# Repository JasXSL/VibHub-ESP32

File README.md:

# VibHub-ESP32
Beefing up the HW of VibHub

This is the firmware for the ESP32 version.
If you're looking for the API documentation, you can find that on the original VibHub client git: 
https://github.com/JasXSL/VibHub-Client/wiki

Official website: https://vibhub.io

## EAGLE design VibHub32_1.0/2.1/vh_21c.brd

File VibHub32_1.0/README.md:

# VibHub ESP32 Board 2.x

## 2.0a (Shipped 2019)

ESP32 based dev boards shipped in 2019
Replaced by 2.1

## 2.1 rev.A (Unreleased)

Complete board redesign

Add: Lower BOM cost
Changed: Smaller board size
Changed: Moved all buttons to top side of board
Changed: Removed duplicate vibe ports, replaced with combined footprint, can have 4 ports of any combination of 2.5mm and USB
Removed: Extra debug headers and LEDs

Bug: Missing trace that prevents USB-UART chip from powering

## 2.1 rev.B (Unreleased)

Unreleased
50% board redesign due to new battery holder to replace previous that became unavailable

Add: Second RGB LED
Add: More mounting holes
Add: True auto power off while on battery
Add: Side firing LEDs on driver outputs (Only works if drivers are in "forward")
Changed: Replaced electrolytic cap with tantalum to reduce component side height clearance

Bug: High leakage current through TX line while running on battery

## 2.1 rev.C (In Production)

First batch of 30 dev boards currently in production as of 2020-03-04, should be shipping by mid March

Bug: Designator and pin 1 marking missing on D1

## 2.1 rev.C2 (Design In Progress)

Tentative revision for next batch
Identical to rev.C with only silkscreen modifications

## 2.1 rev.D (Planning)

Future TODO stuff

TODO: Replace DRV8833 footprint with QFN16 after supply of HTSSOP16 parts has been used. The HTSSOP16/QFN16 combo footprint works but is more difficult to reflow than needed.

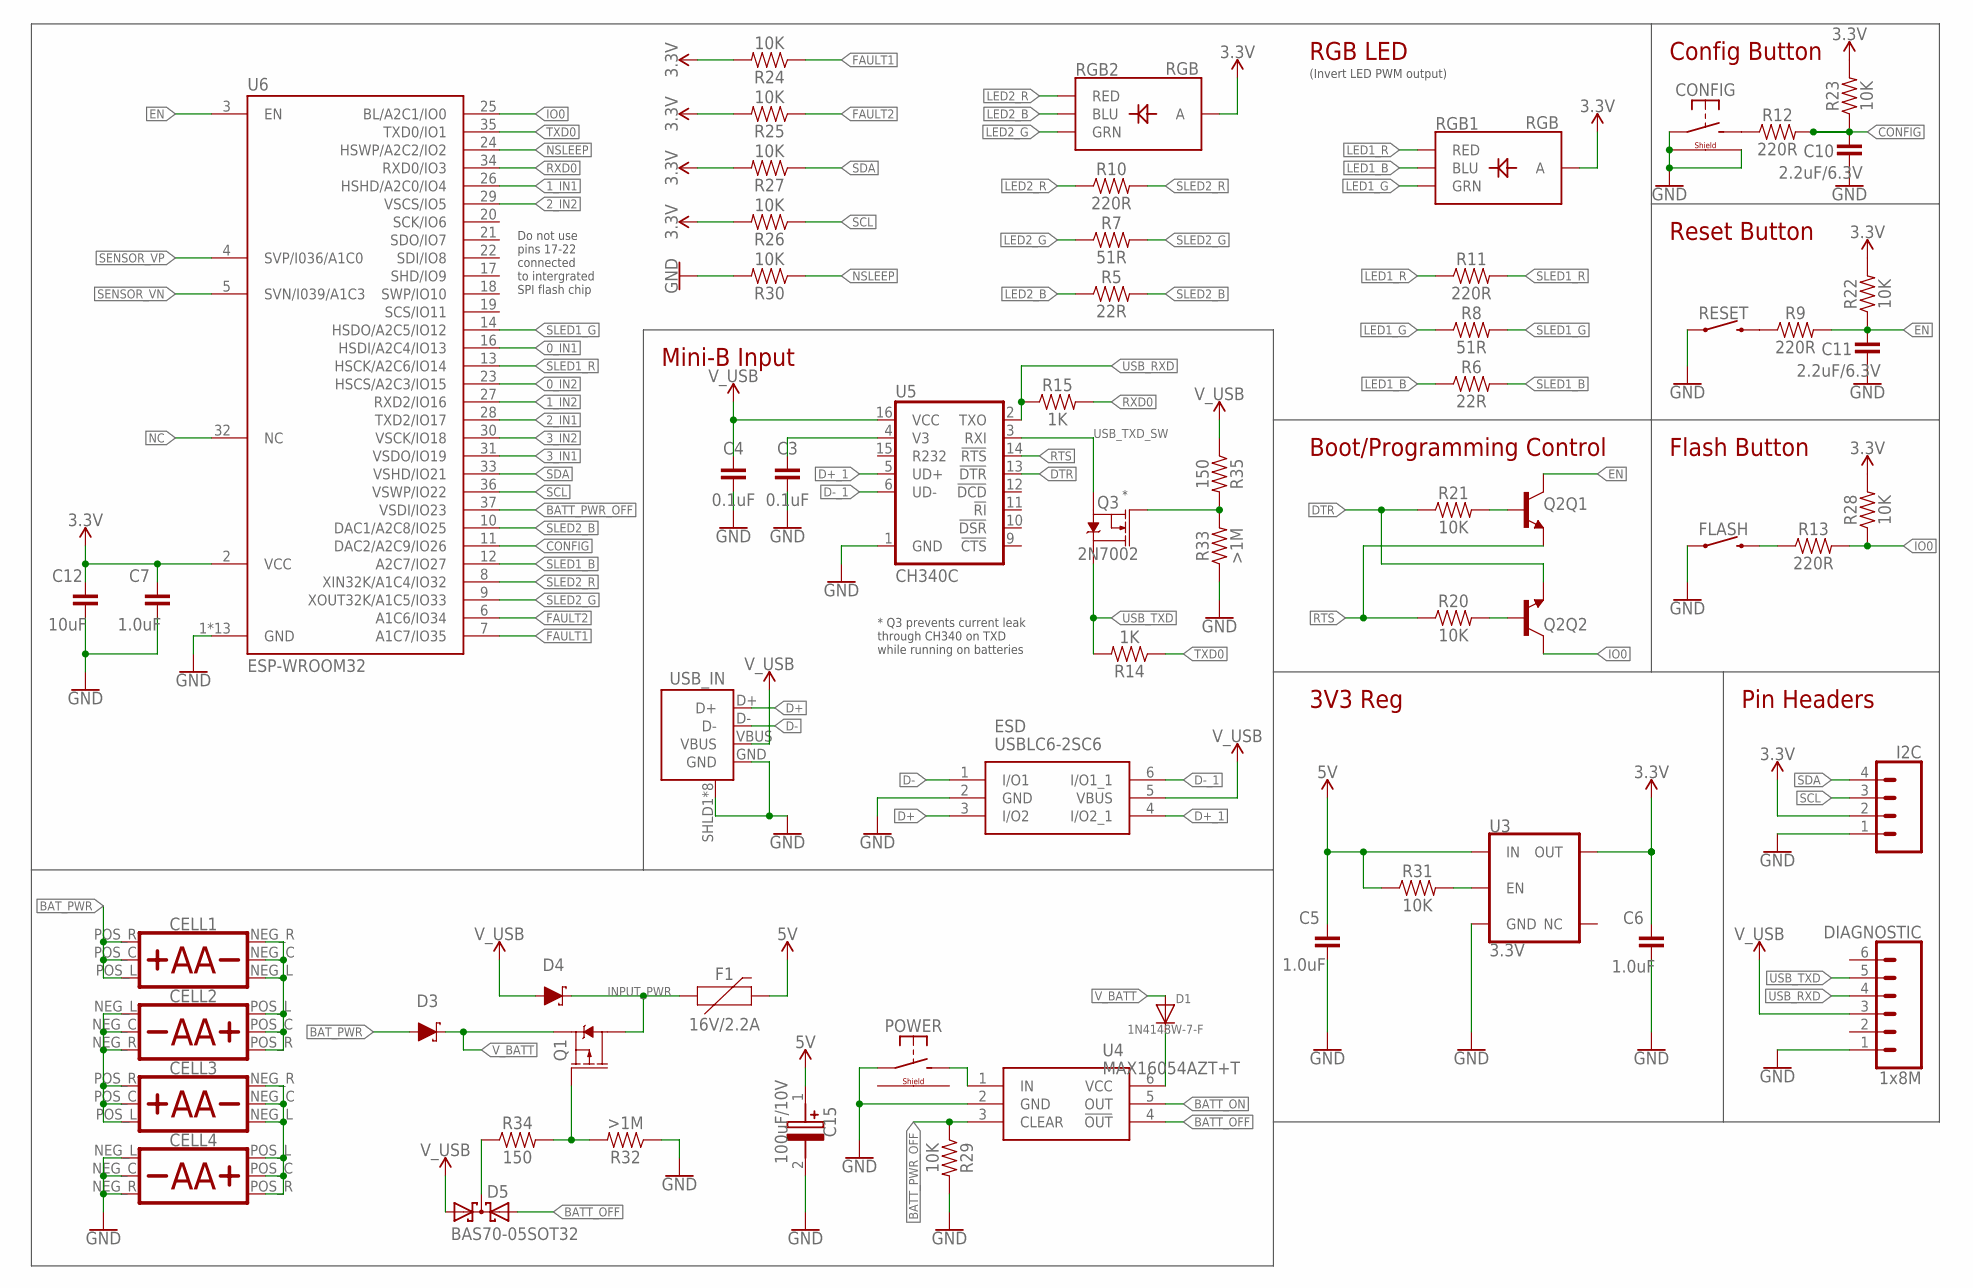
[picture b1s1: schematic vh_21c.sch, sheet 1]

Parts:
C3, C4: 0.1uF; C0805
C5, C6, C7: 1.0uF; C0805
C10, C11: 2.2uF/6.3V; C0805
C12: 10uF; C0805
C15: 100uF/10V; CAPPM6032X270N
CELL1, CELL2, CELL3, CELL4: AA_590_596
CONFIG: MOMENTARY-SWITCH-SPST-RIGHTSQ75; SW6X6_RIGHT_SQ73
D1: 1N4148W-7-F; SOD-123
D3, D4: 3A/40V/500mV; SMA-DIODE
D5: BAS70-05SOT32; SOT91P240X110-3
DIAGNOSTIC: 1x8M; 1X06_LOCK
ESD: USBLC6-2SC6; SOT95P280X145-6N
F1: 16V/2.2A; FUSC7035X90
FLASH: MOMENTARY-SWITCH-SPST-SMD-6.0X3.5MM; TACTILE_SWITCH_SMD_6.0X3.5MM
I2C: CONN_04; 1X04
POWER: MOMENTARY-SWITCH-SPST-RIGHTSQ75; SW6X6_RIGHT_SQ73
Q1: MOSFET_PCH-DMG2305UX-13; SOT91P240X110-3
Q2: TRANS_NPN_DUAL-MBT3904DW1T1; SC70-6
Q3: 2N7002; SOT23-3
R5, R6: 22R; 0805
R7, R8: 51R; 0805
R9, R10, R11, R12, R13: 220R; 0805
R14, R15: 1K; 0805
R20, R21, R22, R23, R24, R25, R26, R27, R28, R29, R30, R31: 10K; 0805
R32, R33: >1M; 0805
R34, R35: 150; 0805
RESET: MOMENTARY-SWITCH-SPST-SMD-6.0X3.5MM; TACTILE_SWITCH_SMD_6.0X3.5MM
RGB1, RGB2: RGB; P-LCC-4-3
U3: 3.3V; SOT23-5
U4: MAX16054AZT+T; SOT95P275X110-6N
U5: CH340C; SO016
U6: ESP-WROOM32
USB_IN: USB-MICROB-2; USB-MICROB-10118194

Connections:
0_IN1: U6.16 (HSDI/A2C4/IO13); also elsewhere on the board
0_IN2: U6.23 (HSCS/A2C3/IO15); also elsewhere on the board
1_IN1: U6.26 (HSHD/A2C0/IO4); also elsewhere on the board
1_IN2: U6.27 (RXD2/IO16); also elsewhere on the board
2_IN1: U6.28 (TXD2/IO17); also elsewhere on the board
2_IN2: U6.29 (VSCS/IO5); also elsewhere on the board
3.3V: C6.1, C7.1, C12.1, I2C.2, R22.2, R23.2, R24.2, R25.2, R26.2, R27.2, R28.2, RGB1.4 (A), RGB2.4 (A), U3.5 (OUT), U6.2 (VCC)
3_IN1: U6.31 (VSDO/IO19); also elsewhere on the board
3_IN2: U6.30 (VSCK/IO18); also elsewhere on the board
5V: C5.1, C15.1 (+), F1.2, R31.1, U3.1 (IN); also elsewhere on the board
BATT_OFF: D5.2 (A2), U4.4 (!OUT)
BATT_ON: U4.5 (OUT)
BATT_PWR_OFF: R29.1, U4.3 (CLEAR), U6.37 (VSDI/IO23)
BAT_PWR: CELL1.POS_C, CELL1.POS_L, CELL1.POS_R, D3.A
CONFIG: C10.1, R12.2, R23.1, U6.11 (DAC2/A2C9/IO26)
D+: ESD.3 (I/O2), USB_IN.D+
D+_1: ESD.4 (I/O2_1), U5.5 (UD+)
D-: ESD.1 (I/O1), USB_IN.D-
D-_1: ESD.6 (I/O1_1), U5.6 (UD-)
DTR: Q2.1 (E), R21.1, U5.13 (!DTR)
EN: C11.1, Q2.3 (C), R9.2, R22.1, U6.3 (EN)
EN_BASE: Q2.5 (B), R21.2
FAULT1: R24.1, U6.7 (A1C7/IO35); also elsewhere on the board
FAULT2: R25.1, U6.6 (A1C6/IO34); also elsewhere on the board
GND: C3.2, C4.2, C5.2, C6.2, C7.2, C10.2, C11.2, C12.2, C15.2 (-), CELL4.NEG_C, CELL4.NEG_L, CELL4.NEG_R, CONFIG.2 (P1), CONFIG.SHLD@1 (SHIELD1), CONFIG.SHLD@2 (SHIELD2), DIAGNOSTIC.1, ESD.2 (GND), FLASH.1, I2C.1, POWER.2 (P1), R29.2, R30.2, R32.1, R33.1, RESET.1, U3.2 (GND), U4.2 (GND), U5.1 (GND), U6.1 (GND), U6.15 (GND), U6.38 (GND), U6.TP (GND), U6.TP1 (GND), U6.TP2 (GND), U6.TP3 (GND), U6.TP4 (GND), U6.TP5 (GND), U6.TP6 (GND), U6.TP7 (GND), U6.TP8 (GND), U6.TP9 (GND), USB_IN.GND, USB_IN.SHLD1 (SHIELD), USB_IN.SHLD2 (SHIELD), USB_IN.SHLD3 (SHIELD), USB_IN.SHLD4 (SHIELD), USB_IN.SHLD5 (SHIELD), USB_IN.SHLD6 (SHIELD), USB_IN.SHLD7 (SHIELD), USB_IN.SHLD8 (SHIELD); also elsewhere on the board
INPUT_PWR: D4.C, F1.1, Q1.3 (D)
IO0: Q2.6 (C), R13.2, R28.1, U6.25 (BL/A2C1/IO0)
IO0_BASE: Q2.2 (B), R20.2
LED1_B: R6.1, RGB1.3 (BLU)
LED1_G: R8.1, RGB1.2 (GRN)
LED1_R: R11.1, RGB1.1 (RED)
LED2_B: R5.1, RGB2.3 (BLU)
LED2_G: R7.1, RGB2.2 (GRN)
LED2_R: R10.1, RGB2.1 (RED)
unnamed: R31.2, U3.3 (EN)
unnamed: C3.1, U5.4 (V3)
unnamed: D5.3 (C), R34.1
unnamed: POWER.1 (S1), U4.1 (IN)
unnamed: D1.C, U4.6 (VCC)
unnamed: R9.1, RESET.2
unnamed: CELL1.NEG_C, CELL1.NEG_L, CELL1.NEG_R, CELL2.POS_C, CELL2.POS_L, CELL2.POS_R
unnamed: CELL2.NEG_C, CELL2.NEG_L, CELL2.NEG_R, CELL3.POS_C, CELL3.POS_L, CELL3.POS_R
unnamed: CELL3.NEG_C, CELL3.NEG_L, CELL3.NEG_R, CELL4.POS_C, CELL4.POS_L, CELL4.POS_R
unnamed: CONFIG.1 (S1), R12.1
unnamed: Q1.1 (G), R32.2, R34.2
unnamed: Q3.1 (G), R33.2, R35.2
unnamed: FLASH.2, R13.1
NC: U6.32 (NC)
NSLEEP: R30.1, U6.24 (HSWP/A2C2/IO2); also elsewhere on the board
RTS: Q2.4 (E), R20.1, U5.14 (!RTS)
RXD0: R15.2, U6.34 (RXD0/IO3)
SCL: I2C.3, R26.1, U6.36 (VSWP/IO22)
SDA: I2C.4, R27.1, U6.33 (VSHD/IO21)
SENSOR_VN: U6.5 (SVN/I039/A1C3)
SENSOR_VP: U6.4 (SVP/I036/A1C0)
SLED1_B: R6.2, U6.12 (A2C7/IO27)
SLED1_G: R8.2, U6.14 (HSDO/A2C5/IO12)
SLED1_R: R11.2, U6.13 (HSCK/A2C6/IO14)
SLED2_B: R5.2, U6.10 (DAC1/A2C8/IO25)
SLED2_G: R7.2, U6.9 (XOUT32K/A1C5/IO33)
SLED2_R: R10.2, U6.8 (XIN32K/A1C4/IO32)
TXD0: R14.1, U6.35 (TXD0/IO1)
USB_RXD: DIAGNOSTIC.4, R15.1, U5.2 (TXO)
USB_TXD: DIAGNOSTIC.5, Q3.3 (D), R14.2
USB_TXD_SW: Q3.2 (S), U5.3 (RXI)
V_BATT: D1.A, D3.C, Q1.2 (S)
V_USB: C4.1, D4.A, D5.1 (A1), DIAGNOSTIC.3, ESD.5 (VBUS), R35.1, U5.16 (VCC), USB_IN.VBUS

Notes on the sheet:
(Invert LED PWM output)
Reset Button
Config Button
RGB LED
Boot/Programming Control
Pin Headers
Mini-B Input
Flash Button
Do not use pins 17-22 connected to intergrated SPI flash chip
3V3 Reg
* Q3 prevents current leak through CH340 on TXD while running on batteries

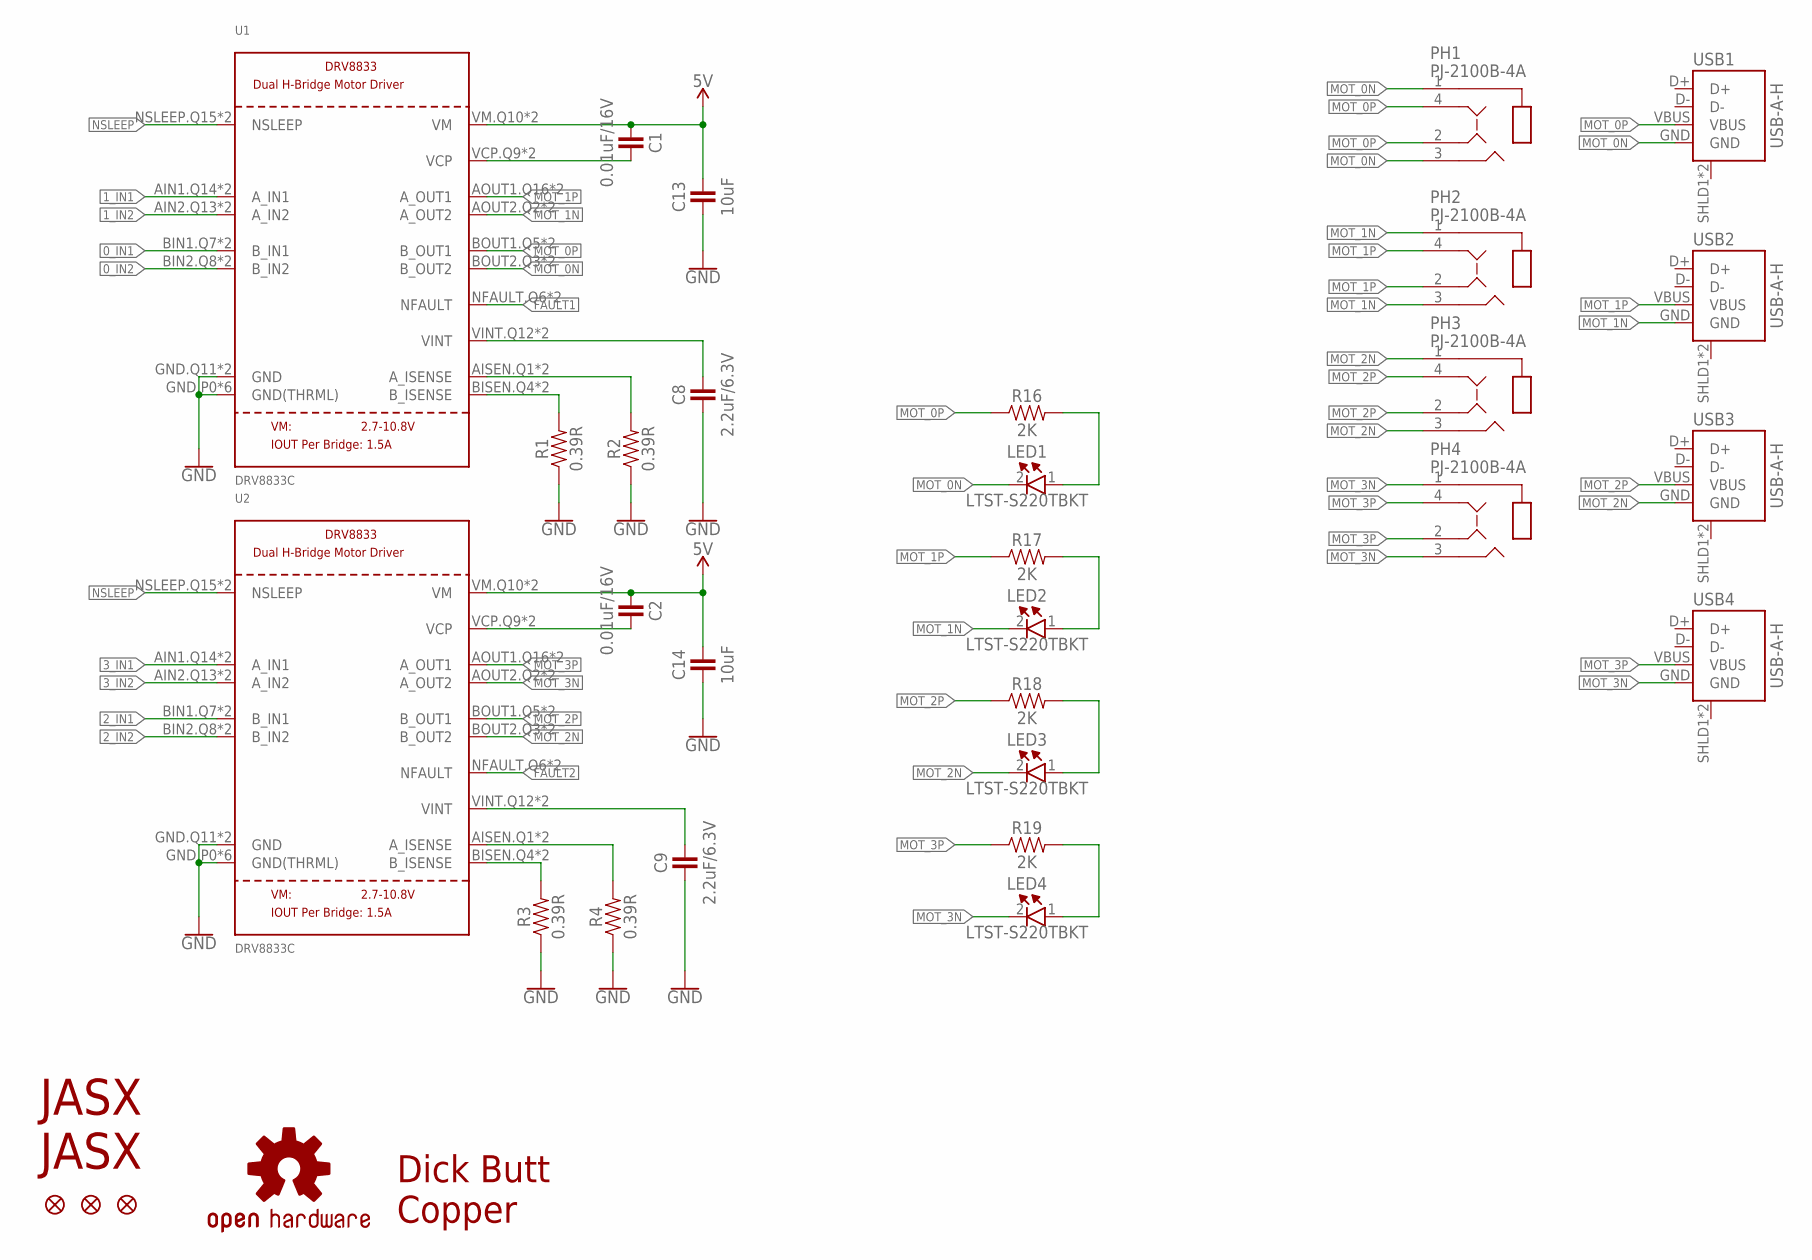
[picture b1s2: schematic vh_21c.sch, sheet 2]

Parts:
C1, C2: 0.01uF/16V; C0805
C8, C9: 2.2uF/6.3V; C0805
C13, C14: 10uF; C0805
FD1, FD2, FD3: FIDUCIAL1X2; FIDUCIAL-1X2
LED1, LED2, LED3, LED4: LTST-S220TBKT; LTST-S220KFKT
LOGO1: OSHW-LOGOM; OSHW-LOGO-M
LOGO2, LOGO4: JASX_LOGO_MID; JASX_LOGO_M
LOGO3: DICKBUTTCOPPER; DICKBUTT_COPPER
PH1, PH2, PH3, PH4: PJ-2100B-4A; PJ2100B4A
R1, R2, R3, R4: 0.39R; 0805
R16, R17, R18, R19: 2K; 0805
U1, U2: DRV8833C; DRV8833_COMBO
USB1, USB2, USB3, USB4: USB-A-H

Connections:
0_IN1: U1.BIN1.Q7 (B_IN1), U1.BIN1.T9 (B_IN1); also elsewhere on the board
0_IN2: U1.BIN2.Q8 (B_IN2), U1.BIN2.T10 (B_IN2); also elsewhere on the board
1_IN1: U1.AIN1.Q14 (A_IN1), U1.AIN1.T16 (A_IN1); also elsewhere on the board
1_IN2: U1.AIN2.Q13 (A_IN2), U1.AIN2.T15 (A_IN2); also elsewhere on the board
2_IN1: U2.BIN1.Q7 (B_IN1), U2.BIN1.T9 (B_IN1); also elsewhere on the board
2_IN2: U2.BIN2.Q8 (B_IN2), U2.BIN2.T10 (B_IN2); also elsewhere on the board
3_IN1: U2.AIN1.Q14 (A_IN1), U2.AIN1.T16 (A_IN1); also elsewhere on the board
3_IN2: U2.AIN2.Q13 (A_IN2), U2.AIN2.T15 (A_IN2); also elsewhere on the board
5V: C1.1, C2.1, C13.2, C14.2, U1.VM.Q10 (VM), U1.VM.T12 (VM), U2.VM.Q10 (VM), U2.VM.T12 (VM); also elsewhere on the board
A_ISENSE0: R2.2, U1.AISEN.Q1 (A_ISENSE), U1.AISEN.T3 (A_ISENSE)
A_ISENSE1: R4.2, U2.AISEN.Q1 (A_ISENSE), U2.AISEN.T3 (A_ISENSE)
B_ISENSE0: R1.2, U1.BISEN.Q4 (B_ISENSE), U1.BISEN.T6 (B_ISENSE)
B_ISENSE1: R3.2, U2.BISEN.Q4 (B_ISENSE), U2.BISEN.T6 (B_ISENSE)
FAULT1: U1.NFAULT.Q6 (NFAULT), U1.NFAULT.T8 (NFAULT); also elsewhere on the board
FAULT2: U2.NFAULT.Q6 (NFAULT), U2.NFAULT.T8 (NFAULT); also elsewhere on the board
GND: C8.1, C9.1, C13.1, C14.1, R1.1, R2.1, R3.1, R4.1, U1.GND.P0 (GND(THRML)), U1.GND.P1 (GND(THRML)), U1.GND.P2 (GND(THRML)), U1.GND.P3 (GND(THRML)), U1.GND.P4 (GND(THRML)), U1.GND.P5 (GND(THRML)), U1.GND.Q11 (GND), U1.GND.T13 (GND), U2.GND.P0 (GND(THRML)), U2.GND.P1 (GND(THRML)), U2.GND.P2 (GND(THRML)), U2.GND.P3 (GND(THRML)), U2.GND.P4 (GND(THRML)), U2.GND.P5 (GND(THRML)), U2.GND.Q11 (GND), U2.GND.T13 (GND); also elsewhere on the board
MOT_0N: LED1.2 (K), PH1.1, PH1.3, U1.BOUT2.Q3 (B_OUT2), U1.BOUT2.T5 (B_OUT2), USB1.GND
MOT_0P: PH1.2, PH1.4, R16.1, U1.BOUT1.Q5 (B_OUT1), U1.BOUT1.T7 (B_OUT1), USB1.VBUS
MOT_1N: LED2.2 (K), PH2.1, PH2.3, U1.AOUT2.Q2 (A_OUT2), U1.AOUT2.T4 (A_OUT2), USB2.GND
MOT_1P: PH2.2, PH2.4, R17.1, U1.AOUT1.Q16 (A_OUT1), U1.AOUT1.T2 (A_OUT1), USB2.VBUS
MOT_2N: LED3.2 (K), PH3.1, PH3.3, U2.BOUT2.Q3 (B_OUT2), U2.BOUT2.T5 (B_OUT2), USB3.GND
MOT_2P: PH3.2, PH3.4, R18.1, U2.BOUT1.Q5 (B_OUT1), U2.BOUT1.T7 (B_OUT1), USB3.VBUS
MOT_3N: LED4.2 (K), PH4.1, PH4.3, U2.AOUT2.Q2 (A_OUT2), U2.AOUT2.T4 (A_OUT2), USB4.GND
MOT_3P: PH4.2, PH4.4, R19.1, U2.AOUT1.Q16 (A_OUT1), U2.AOUT1.T2 (A_OUT1), USB4.VBUS
unnamed: LED1.1 (A), R16.2
unnamed: LED2.1 (A), R17.2
unnamed: LED3.1 (A), R18.2
unnamed: LED4.1 (A), R19.2
NSLEEP: U1.NSLEEP.Q15 (NSLEEP), U1.NSLEEP.T1 (NSLEEP), U2.NSLEEP.Q15 (NSLEEP), U2.NSLEEP.T1 (NSLEEP); also elsewhere on the board
VCP0: C1.2, U1.VCP.Q9 (VCP), U1.VCP.T11 (VCP)
VCP1: C2.2, U2.VCP.Q9 (VCP), U2.VCP.T11 (VCP)
VINT0: C8.2, U1.VINT.Q12 (VINT), U1.VINT.T14 (VINT)
VINT1: C9.2, U2.VINT.Q12 (VINT), U2.VINT.T14 (VINT)

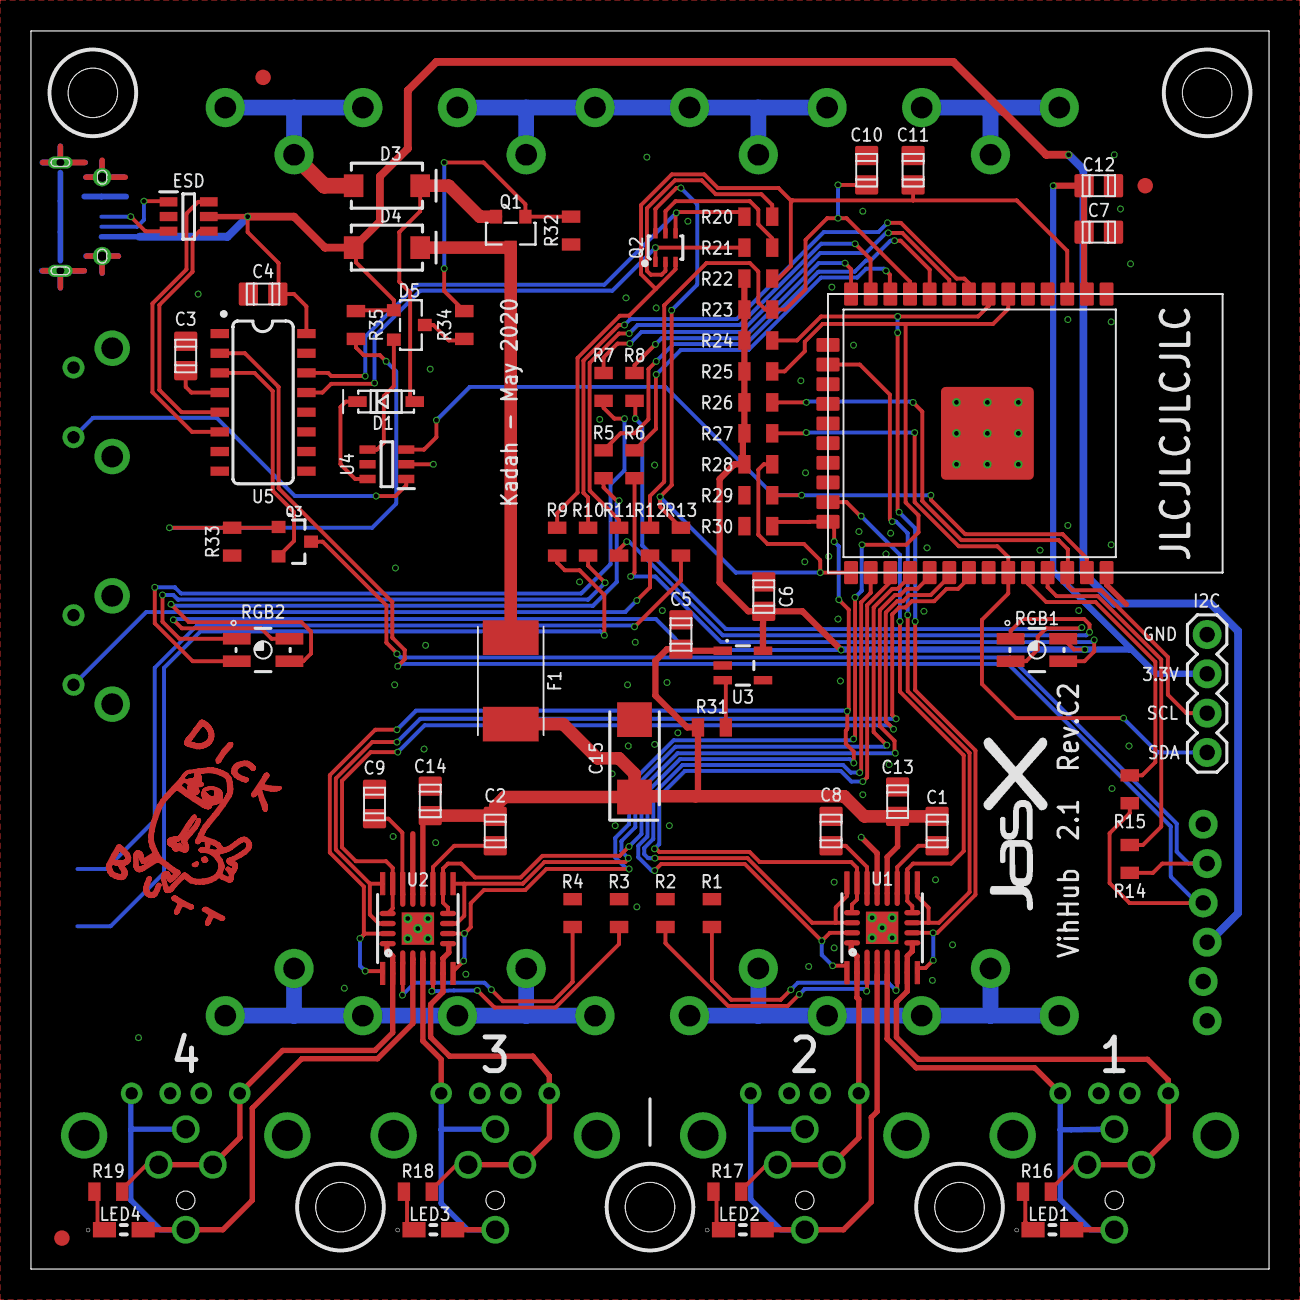
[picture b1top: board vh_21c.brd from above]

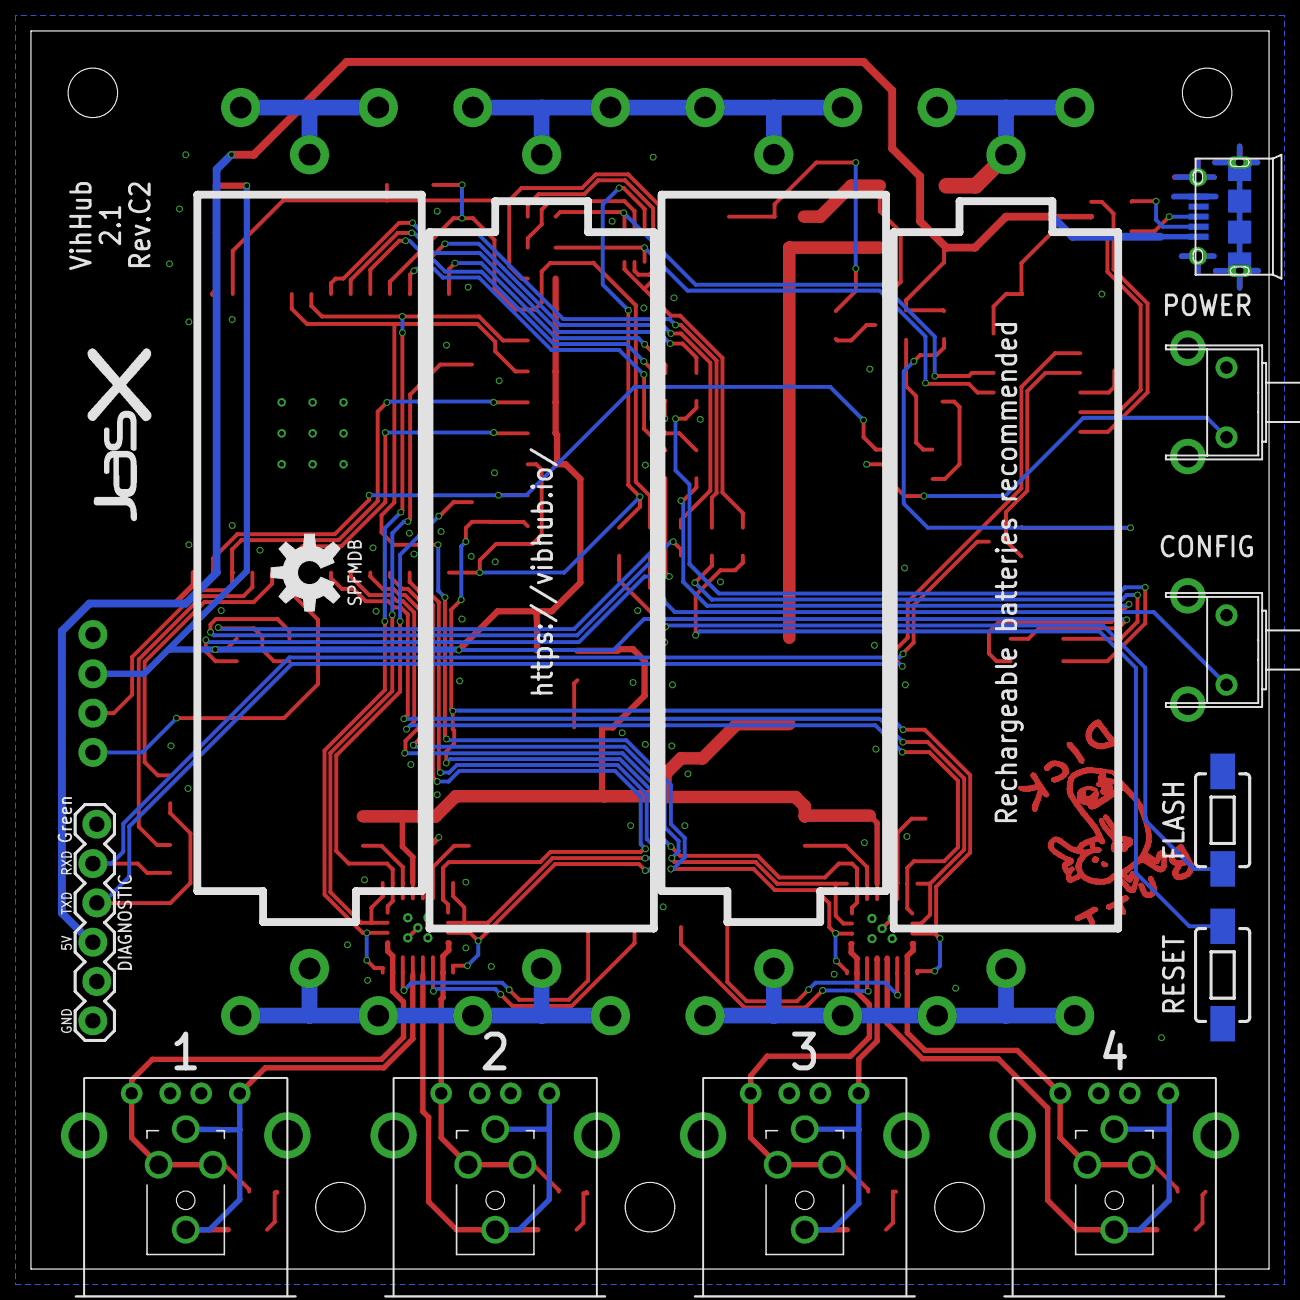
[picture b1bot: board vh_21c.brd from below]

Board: 2 copper layers, 80.0 x 80.0 mm, 97 parts (20 on the bottom side), 83 nets.

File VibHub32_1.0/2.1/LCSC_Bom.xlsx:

Quantity | Value | Description | LCSC Part Number | Package | Customer Part Number
2 | 0.01uF (10nF) / 16V | Capacitors | C107135 | C0805 | C1, C2
3 | 10uF | Capacitors | C15850 | C0805 | C12, C13, C14
1 | 100uF / 10V | Cap Tant Solid 100uF 16V C CASE 10% (6 X 3.2 X 2.5mm) Inward L SMD 6032-27 0.7 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 | C273664 | CAPPM6032X270N | C15
2 | 0.1uF (100nF) | Capacitors | C1760 | C0805 | C3, C4
3 | 1.0uF | Capacitors | C16834 | C0805 | C5, C6, C7
4 | 2.2uF / 6.3V | Capacitors | C364318 | C0805 | C8, C9, C10, C11
1 | 1N4148W-7-F | Diode | C83528 | SOD-123 | D1
2 | B340A-13-F | Schottky diode | C85098 | SMA | D3, D4
1 | BAS70-05W,115 | Silicon Schottky Diodes | C34489 | SOT-23 | D5
1 | USBLC6-2SC6 | TVS Diode Array Uni-Directional USBLC6-2SC6 17V, SOT-23 6-Pin | C7519 | SOT-23-6 | ESD
1 | 16V/2.5A | Resettable Fuse PPTC | C70120 | 1812 | F1
1 | DMG2305UX-13 | P-channel MOSFETs | C144153 | SOT91P240X110-3 | Q1
1 | MBT3904DW1T1G | Dual NPN Transistors in Single Package | C110150 | SC70-6 | Q2
1 | 2N7002,215 | N-channel MOSFETs | C65189 | SOT23-3 | Q3
4 | 0.30R to 0.40R | Generic Resistor Package | C247135 | R0805 | R1, R2, R3, R4
2 | 22R | Generic Resistor Package | C107702 | R0805 | R5, R6
2 | 51R | Generic Resistor Package | C114537 | R0805 | R7, R8
5 | 220R | Generic Resistor Package | C114519 | R0805 | R9, R10, R11, R12, R13
2 | 1K | Generic Resistor Package | C100046 | R0805 | R14, R15
4 | 2K | Generic Resistor Package | C114748 | R0805 | R16, R17, R18, R19
12 | 10K | Generic Resistor Package | C84376 | R0805 | R20, R21, R22, R23, R24, R25, R26, R27, R28, R29, R30, R31
1 | >1M | Generic Resistor Package | C137463 | R0805 | R32, R33
2 | 150R (or 220R) | Generic Resistor Package | C114523 | R0805 | R34, R35
2 | DRV8833C | DRV8833 Dual H-Bridge Motor Driver | C154936 | HTSSOP16 or QFN16 | U1, U2
1 | AP2112K-3.3V | AP2112 - 600mA CMOS LDO Regulator w/ Enable | C51118 | SOT23-5 | U3
1 | MAX16054AZT+T | On Off Controller, Debounce, 15kV ESD MAX16054AZT+T, Voltage Supervisor No Push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 | C79401 | SOT95P275X110-6N | U4
1 | CH340C |  | C84681 | SO016 | U5
4 | LTST-S220TBKT | LED,0805,Side View,Blue,30mcd Lite-On LTST-S220TBKT Blue LED, 475 nm 2012 (0805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 | C284936 | LTST-S220KFKT | LED1, LED2, LED3, LED4
2 | RGB | LED-RGB Diffused Common Anode | C108539 | P-LCC-4-3 | RGB1, RGB2
1 | ESP-WROOM32 | Espressif ESP-WROOM-32 | C95209 | ESP-WROOM32 | U6
1 | USB-MICROB-2 | Micro USB Connector | C319164 | USB-MICROB-10118194 | USB_IN
2 | MOMENTARY-SWITCH-SPST-RIGHTSQ75 | 6x6 right angle tact switch | C127680 | SW6X6_RIGHT_SQ73 | CONFIG, POWER
2 | MOMENTARY-SWITCH-SPST-SMD-6.0X3.5MM | SMD tact switch | C329185 | TACTILE_SWITCH_SMD_6.0X3.5MM | FLASH, RESET
4 | USB-A-H | USB Connectors | C2346 | USB-A-H | USB1, USB2, USB3, USB4
4 | PJ-2100B-4A | Audio & Video Connectors Female 11*5mm RoHS | C145822 | PJ2100B4A | PH1, PH2, PH3, PH4

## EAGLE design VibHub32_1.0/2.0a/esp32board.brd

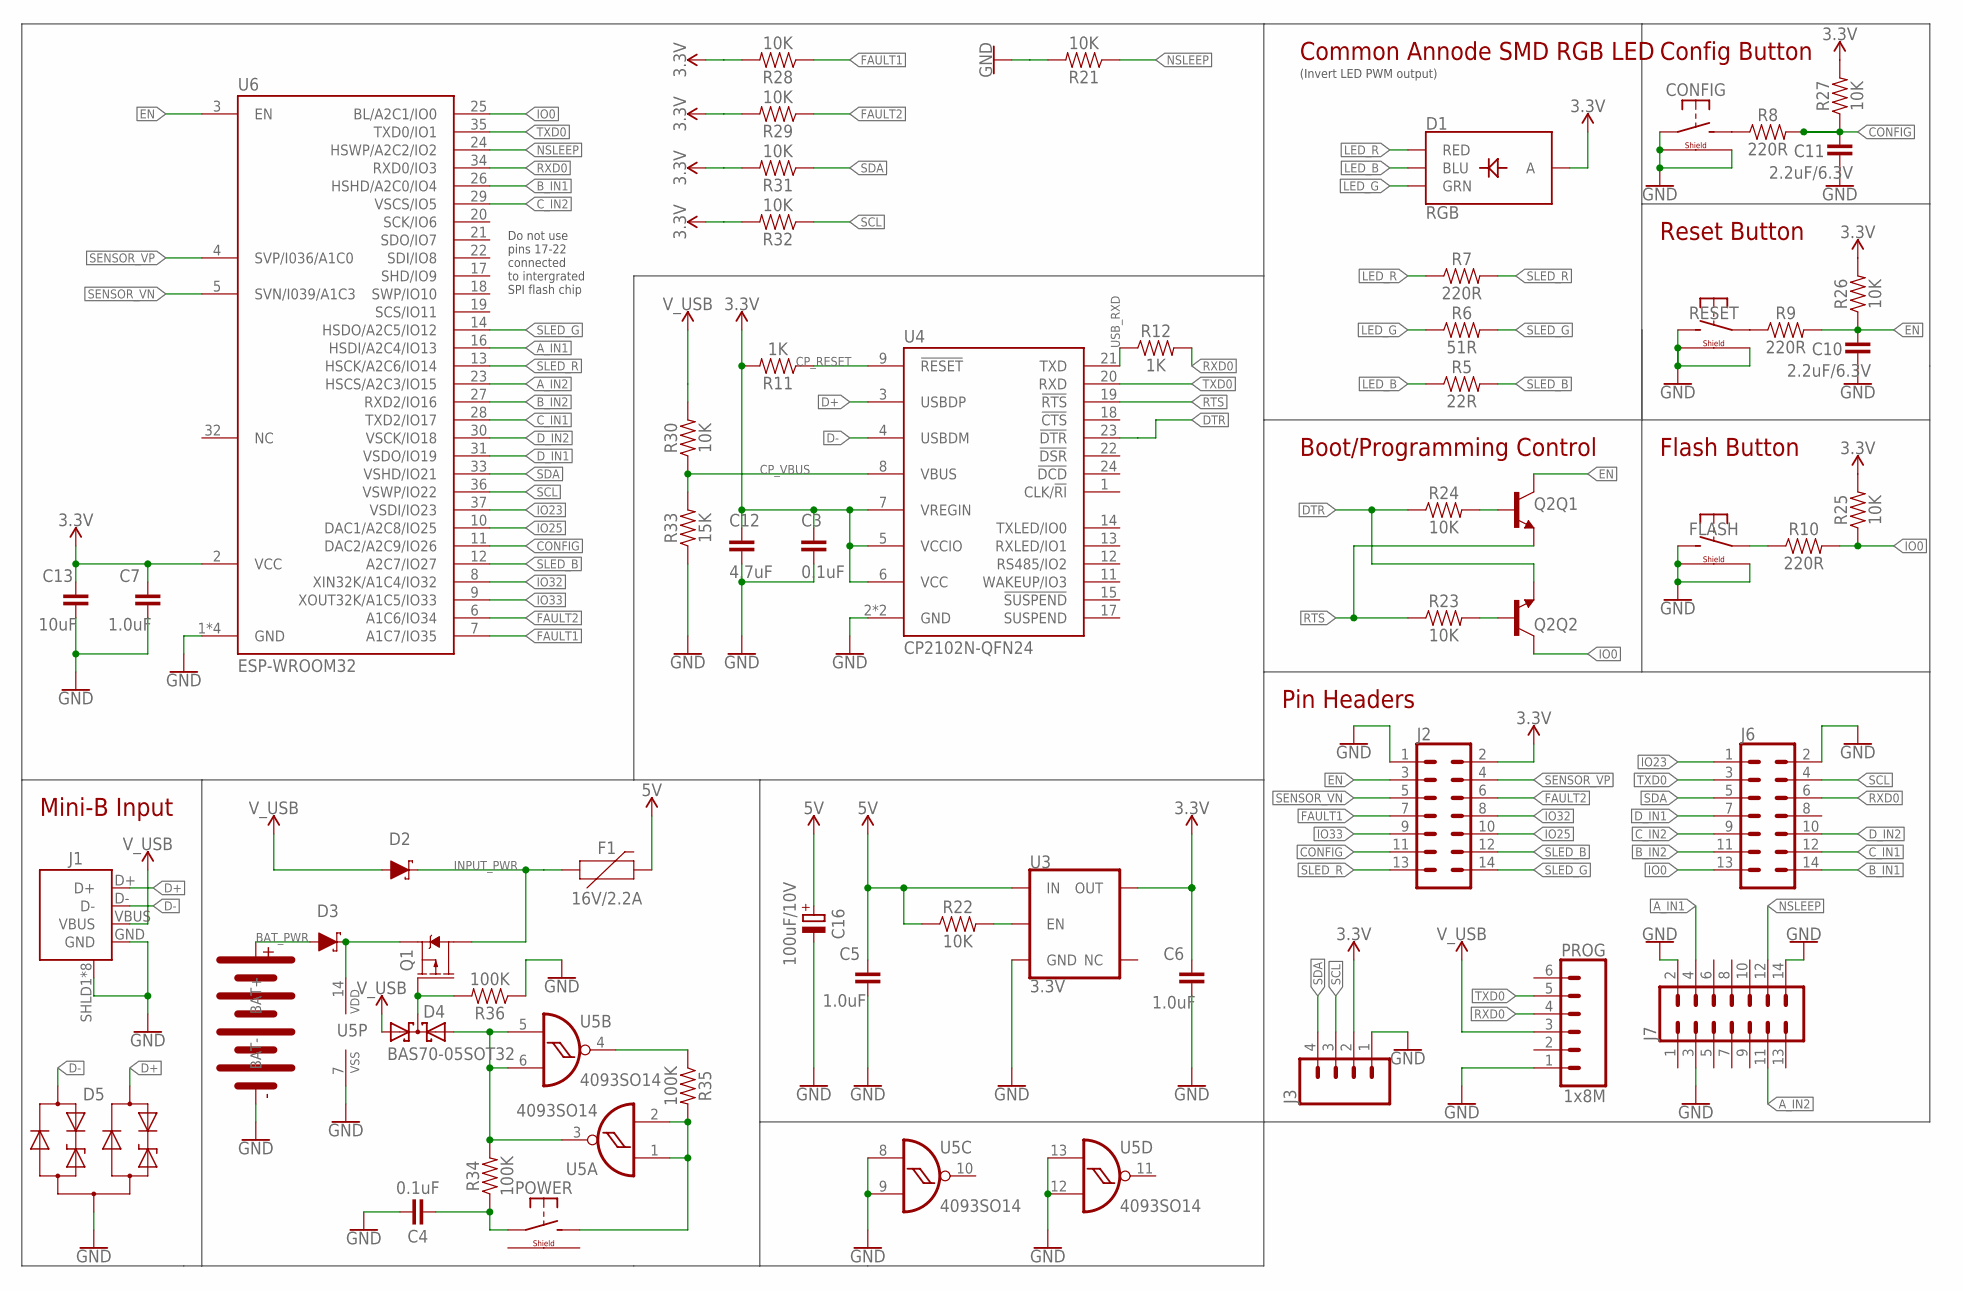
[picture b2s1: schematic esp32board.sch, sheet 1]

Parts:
BAT: BC4AAPCBC4AAPC; BC4AAPC
C3, C4: 0.1uF; C0805
C5, C6, C7: 1.0uF; C0805
C10, C11: 2.2uF/6.3V; C0805
C12: 4.7uF; C0805
C13: 10uF; C0805
C16: 100uF/10V; PANASONIC_D
CONFIG: MOMENTARY-SWITCH-SPST-RIGHTSQ75; SW6X6_RIGHT_SQ73
D1: RGB; P-LCC-4-3
D2, D3: 3A/40V/500mV; SMA-DIODE
D4: BAS70-05SOT32; SOT91P240X110-3
D5: D_ESD5V3U2U-03F; SOT723
F1: 16V/2.2A; FUSC7035X90
FLASH: MOMENTARY-SWITCH-SPST-RIGHTSQ75; SW6X6_RIGHT_SQ73
J1: USB-MICROB-2; USB-MICROB-10118194
J2, J6, J7: CONN_07X2; 2X7
J3: CONN_04; 1X04
POWER: MOMENTARY-SWITCH-SPST-RIGHTSQ75; SW6X6_RIGHT_SQ73
PROG: 1x8M; 1X06_LOCK
Q1: MOSFET_PCH-DMG2305UX-13; SOT91P240X110-3
Q2: TRANS_NPN_DUAL-MBT3904DW1T1; SC70-6
R5: 22R; 0805
R6: 51R; 0805
R7, R8, R9, R10: 220R; 0805
R11, R12: 1K; 0805
R21, R22, R23, R24, R25, R26, R27, R28, R29, R30, R31, R32: 10K; 0805
R33: 15K; 0805
R34, R35, R36: 100K; 0805
RESET: MOMENTARY-SWITCH-SPST-RIGHTSQ75; SW6X6_RIGHT_SQ73
U3: 3.3V; SOT23-5
U4: CP2102N-QFN24; QFN24-PAD
U5: 4093SO14; SOIC127P600X175-14
U6: ESP-WROOM32

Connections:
3.3V: C3.1, C6.1, C7.1, C12.1, C13.1, D1.4 (A), J2.2, J3.2, R11.2, R25.2, R26.2, R27.2, R28.2, R29.2, R31.2, R32.2, U3.5 (OUT), U4.5 (VCCIO), U4.6 (VCC), U4.7 (VREGIN), U6.2 (VCC)
5V: C5.1, C16.+, F1.2, R22.1, U3.1 (IN); also elsewhere on the board
A_IN1: J7.4, U6.16 (HSDI/A2C4/IO13); also elsewhere on the board
A_IN2: J7.11, U6.23 (HSCS/A2C3/IO15); also elsewhere on the board
BAT_PWR: BAT.P$1 (BAT+), D3.A
B_IN1: J6.14, U6.26 (HSHD/A2C0/IO4); also elsewhere on the board
B_IN2: J6.11, U6.27 (RXD2/IO16); also elsewhere on the board
CONFIG: C11.1, J2.11, R8.2, R27.1, U6.11 (DAC2/A2C9/IO26)
CP_RESET: R11.1, U4.9 (!RESET)
CP_VBUS: R30.1, R33.2, U4.8 (VBUS)
C_IN1: J6.12, U6.28 (TXD2/IO17); also elsewhere on the board
C_IN2: J6.9, U6.29 (VSCS/IO5); also elsewhere on the board
D+: D5.2 (C2), J1.D+, U4.3 (USBDP)
D-: D5.1 (C1), J1.D-, U4.4 (USBDM)
DTR: Q2.1 (E), R24.1, U4.23 (!DTR)
D_IN1: J6.7, U6.31 (VSDO/IO19); also elsewhere on the board
D_IN2: J6.10, U6.30 (VSCK/IO18); also elsewhere on the board
EN: C10.1, J2.3, Q2.3 (C), R9.2, R26.1, U6.3 (EN)
EN_BASE: Q2.5 (B), R24.2
FAULT1: J2.7, R28.1, U6.7 (A1C7/IO35); also elsewhere on the board
FAULT2: J2.6, R29.1, U6.6 (A1C6/IO34); also elsewhere on the board
GND: BAT.P$2 (BAT-), C3.2, C4.2, C5.2, C6.2, C7.2, C10.2, C11.2, C12.2, C13.2, C16.-, CONFIG.2 (P1), CONFIG.SHLD@1 (SHIELD1), CONFIG.SHLD@2 (SHIELD2), D5.3 (A), FLASH.1 (S1), FLASH.SHLD@1 (SHIELD1), FLASH.SHLD@2 (SHIELD2), J1.GND, J1.SHLD1 (SHIELD), J1.SHLD2 (SHIELD), J1.SHLD3 (SHIELD), J1.SHLD4 (SHIELD), J1.SHLD5 (SHIELD), J1.SHLD6 (SHIELD), J1.SHLD7 (SHIELD), J1.SHLD8 (SHIELD), J2.1, J3.1, J6.2, J7.2, J7.3, J7.14, PROG.1, R21.2, R33.1, R36.1, RESET.1 (S1), RESET.SHLD@1 (SHIELD1), RESET.SHLD@2 (SHIELD2), U3.2 (GND), U4.2 (GND), U4.TP (GND), U5.7 (VSS), U5.8 (I0), U5.9 (I1), U5.12 (I1), U5.13 (I0), U6.1 (GND), U6.15 (GND), U6.38 (GND), U6.TP (GND); also elsewhere on the board
INPUT_PWR: D2.C, F1.1, Q1.3 (D)
IO0: J6.13, Q2.6 (C), R10.2, R25.1, U6.25 (BL/A2C1/IO0)
IO0_BASE: Q2.2 (B), R23.2
IO23: J6.1, U6.37 (VSDI/IO23)
IO25: J2.10, U6.10 (DAC1/A2C8/IO25)
IO32: J2.8, U6.8 (XIN32K/A1C4/IO32)
IO33: J2.9, U6.9 (XOUT32K/A1C5/IO33)
LED_B: D1.3 (BLU), R5.1
LED_G: D1.2 (GRN), R6.1
LED_R: D1.1 (RED), R7.1
unnamed: R22.2, U3.3 (EN)
unnamed: D3.C, Q1.2 (S), U5.14 (VDD)
unnamed: POWER.1 (S1), R35.2, U5.1 (I0), U5.2 (I1)
unnamed: CONFIG.1 (S1), R8.1
unnamed: D4.2 (A2), R34.2, U5.3 (O), U5.5 (I0), U5.6 (I1)
unnamed: D4.3 (C), Q1.1 (G), R36.2
unnamed: R35.1, U5.4 (O)
unnamed: C4.1, POWER.2 (P1), R34.1
unnamed: FLASH.2 (P1), R10.1
unnamed: R9.1, RESET.2 (P1)
NSLEEP: J7.12, R21.1, U6.24 (HSWP/A2C2/IO2); also elsewhere on the board
RTS: Q2.4 (E), R23.1, U4.19 (!RTS)
RXD0: J6.6, PROG.4, R12.2, U6.34 (RXD0/IO3)
SCL: J3.3, J6.4, R32.1, U6.36 (VSWP/IO22)
SDA: J3.4, J6.5, R31.1, U6.33 (VSHD/IO21)
SENSOR_VN: J2.5, U6.5 (SVN/I039/A1C3)
SENSOR_VP: J2.4, U6.4 (SVP/I036/A1C0)
SLED_B: J2.12, R5.2, U6.12 (A2C7/IO27)
SLED_G: J2.14, R6.2, U6.14 (HSDO/A2C5/IO12)
SLED_R: J2.13, R7.2, U6.13 (HSCK/A2C6/IO14)
TXD0: J6.3, PROG.5, U4.20 (RXD), U6.35 (TXD0/IO1)
USB_RXD: R12.1, U4.21 (TXD)
V_USB: D2.A, D4.1 (A1), J1.VBUS, PROG.3, R30.2

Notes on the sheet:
(Invert LED PWM output)
Reset Button
Config Button
Common Annode SMD RGB LED
Boot/Programming Control
Pin Headers
Mini-B Input
Flash Button
Do not use pins 17-22 connected to intergrated SPI flash chip
